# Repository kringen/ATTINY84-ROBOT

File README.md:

To compile on linux with AVR-GCC and avrdude installed:

1.  Type "make" at the command prompt

2.  Type "make program" at the

The following are set in the MAKEFILE and you may need to change them based on your system:

AVRDUDE_PROGRAMMER = avrispmkII
AVRDUDE_PORT = usb

The above was tested OK on Ubuntu with an AVRISP MKII programmer connected to the serial port.  
I believe this will also work with an arduino used as a programmer.

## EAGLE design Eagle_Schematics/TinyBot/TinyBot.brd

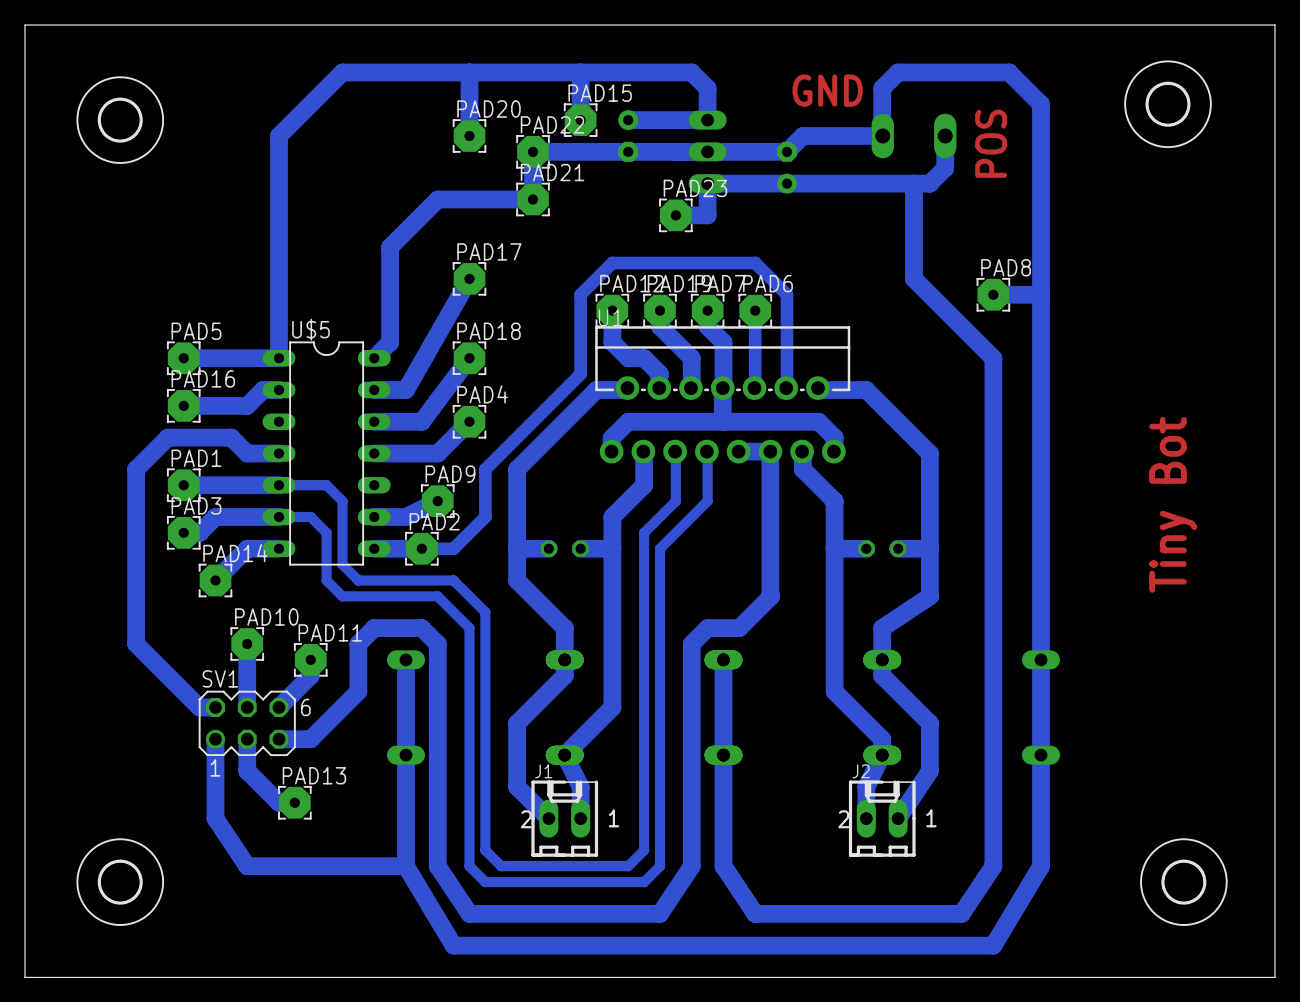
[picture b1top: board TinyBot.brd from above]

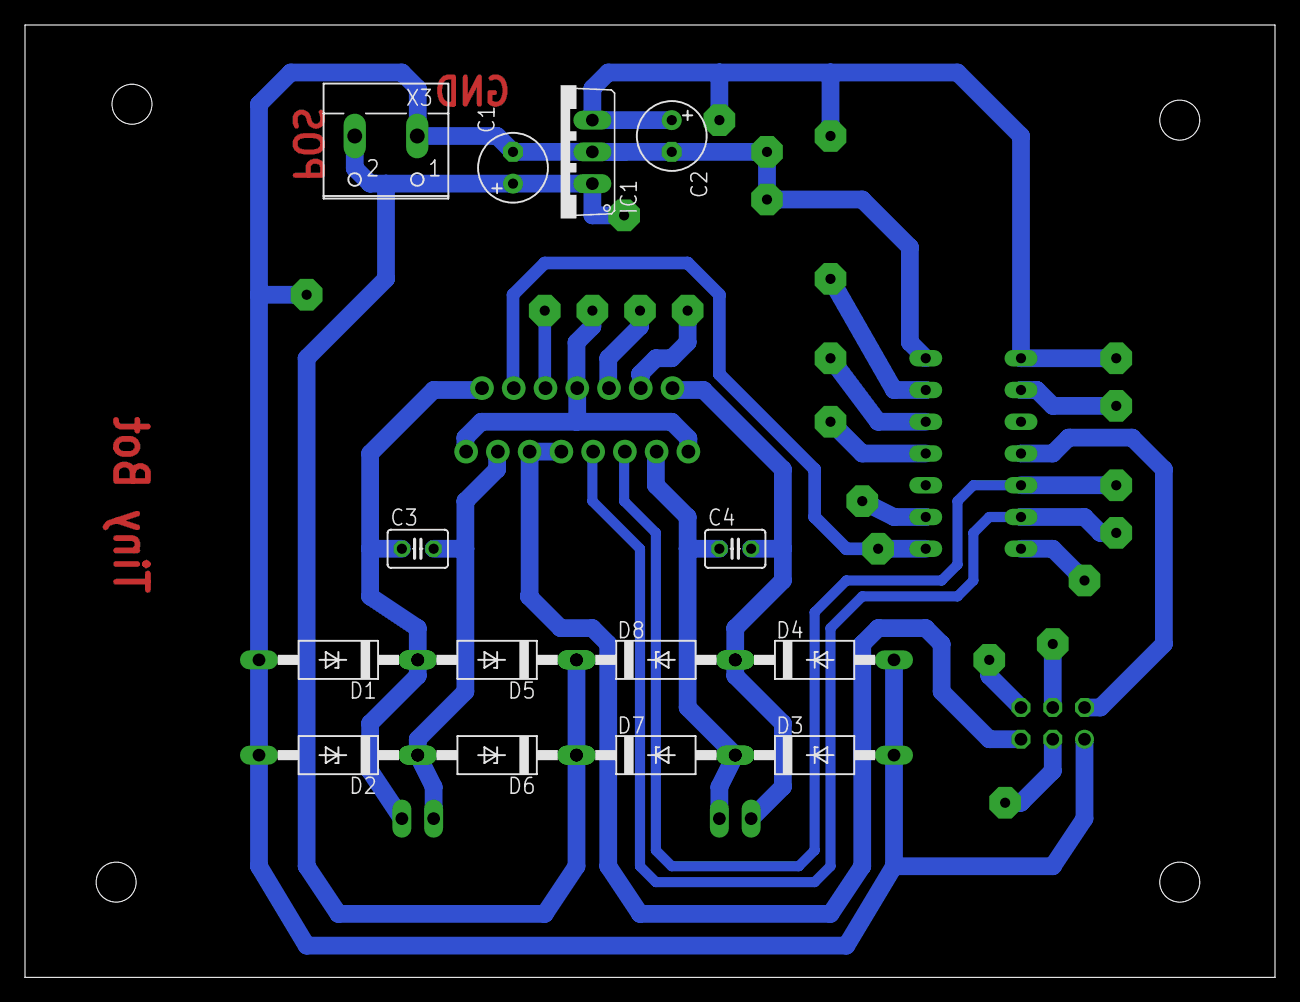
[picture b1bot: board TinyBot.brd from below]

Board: 2 copper layers, 100.0 x 76.2 mm, 46 parts (14 on the bottom side), 17 nets.

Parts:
C1, C2: E2,5-6
C3, C4: C025-030X050
D1, D2, D3, D4, D5, D6, D7, D8: F126Z12
IC1: 7805; TO220V
J1, J2: 22-27-2021-02; 6410-02
PAD1, PAD2, PAD3, PAD4, PAD5, PAD6, PAD7, PAD8, PAD9, PAD10, PAD11, PAD12, PAD13, PAD14, PAD15, PAD16, PAD17, PAD18, PAD19, PAD20, PAD21, PAD22, PAD23: 2,54/0,8
SV1: MA03-2
U1: L298; MULTIWATT15
U$1, U$2, U$3, U$4: 3,2
U$5: ATTINY84; DIL14
X3: W237-102

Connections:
+5V: C2.+, IC1.3, PAD5.1, PAD15.1, PAD19.1, PAD20.1, SV1.5, U1.6, U1.9, U1.11, U$5.1
+12V: C1.+, D5.C, D6.C, D7.C, D8.C, IC1.1, PAD12.1, PAD23.1, U1.4, X3.2
GND: C1.-, C2.-, D1.A, D2.A, D3.A, D4.A, IC1.2, PAD7.1, PAD8.1, PAD21.1, PAD22.1, SV1.1, U1.1, U1.8, U1.15, U$5.14, X3.1
INPUT2: PAD3.1, U1.7, U$5.6
INPUT3: PAD6.1, SV1.3, U1.10, U$5.7
INPUT4: PAD2.1, SV1.6, U1.12, U$5.8
unnamed: SV1.2, U$5.4
unnamed: PAD1.1, U1.5, U$5.5
unnamed: SV1.4, U$5.9
unnamed: PAD16.1, U$5.2
unnamed: PAD17.1, U$5.13
unnamed: PAD18.1, U$5.12
unnamed: PAD4.1, U$5.11
OUT1: C4.2, D4.C, D8.A, J1.2, U1.2
OUT2: C4.1, D3.C, D7.A, J1.1, U1.3
OUT3: C3.2, D2.C, D6.A, J2.2, U1.13
OUT4: C3.1, D1.C, D5.A, J2.1, U1.14

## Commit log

2013-03-30 Included all source files and Eagle schematics
2013-03-30 Added all source files and Eagle schematics.
